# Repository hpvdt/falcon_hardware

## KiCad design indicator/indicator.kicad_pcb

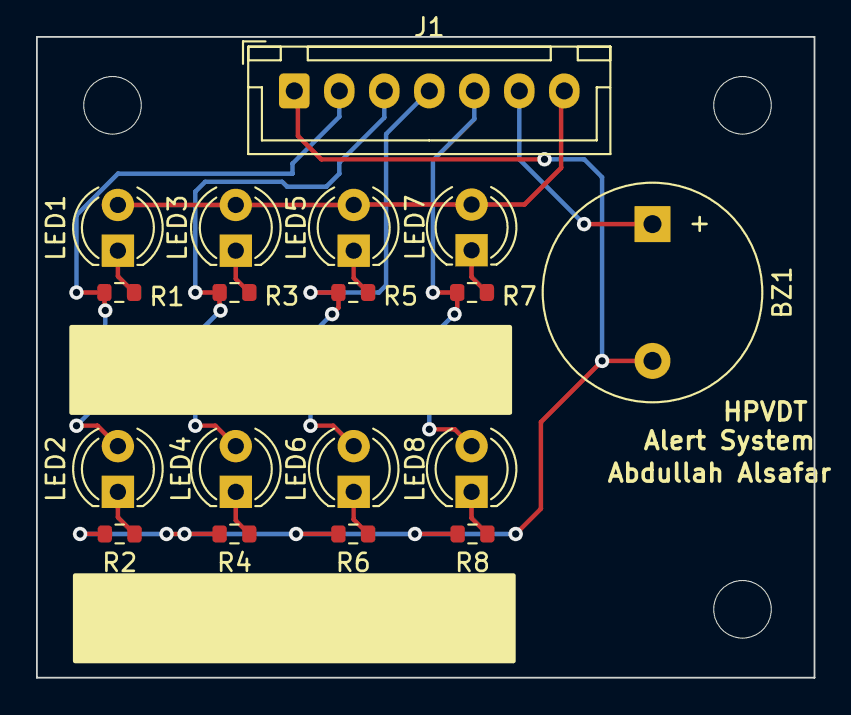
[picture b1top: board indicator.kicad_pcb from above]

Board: 2 copper layers, 43.2 x 35.6 mm, 21 parts (0 on the bottom side), 15 nets.

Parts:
BZ1: Buzzer; Buzzer_12x9.5RM7.6
HOLE1, HOLE2, HOLE3: MountingHole_3.2mm_M3
J1: Conn_01x07_Pin; JST_XH_B7B-XH-A_1x07_P2.50mm_Vertical
LED1: LED2; LED_D4.0mm
LED2: LED3; LED_D4.0mm
LED3: LED4; LED_D4.0mm
LED4: LED5; LED_D4.0mm
LED5: LED6; LED_D4.0mm
LED6: LED7; LED_D4.0mm
LED7: LED8; LED_D4.0mm
LED8: LED9; LED_D4.0mm
R1, R2, R3, R4, R5, R6, R7: 430; R_0603_1608Metric
R8: locked; R_0603_1608Metric

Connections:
+5V: J1.7, LED1.2 (A), LED3.2 (A), LED5.2 (A), LED7.2 (A)
BUZ: BZ1.1 (-), J1.6
GND: BZ1.2 (+), J1.1, R2.1, R4.1, R6.1, R8.1
LED_{FIELD1}: J1.2, LED2.2 (A), R1.1
LED_{FIELD2}: J1.3, LED4.2 (A), R3.1
LED_{FIELD3}: J1.4, LED6.2 (A), R5.1
LED_{FIELD4}: J1.5, LED8.2 (A), R7.1
unnamed: LED1.1 (K), R1.2
unnamed: LED2.1 (K), R2.2
unnamed: LED3.1 (K), R3.2
unnamed: LED4.1 (K), R4.2
unnamed: LED5.1 (K), R5.2
unnamed: LED6.1 (K), R6.2
unnamed: LED7.1 (K), R7.2
unnamed: LED8.1 (K), R8.2

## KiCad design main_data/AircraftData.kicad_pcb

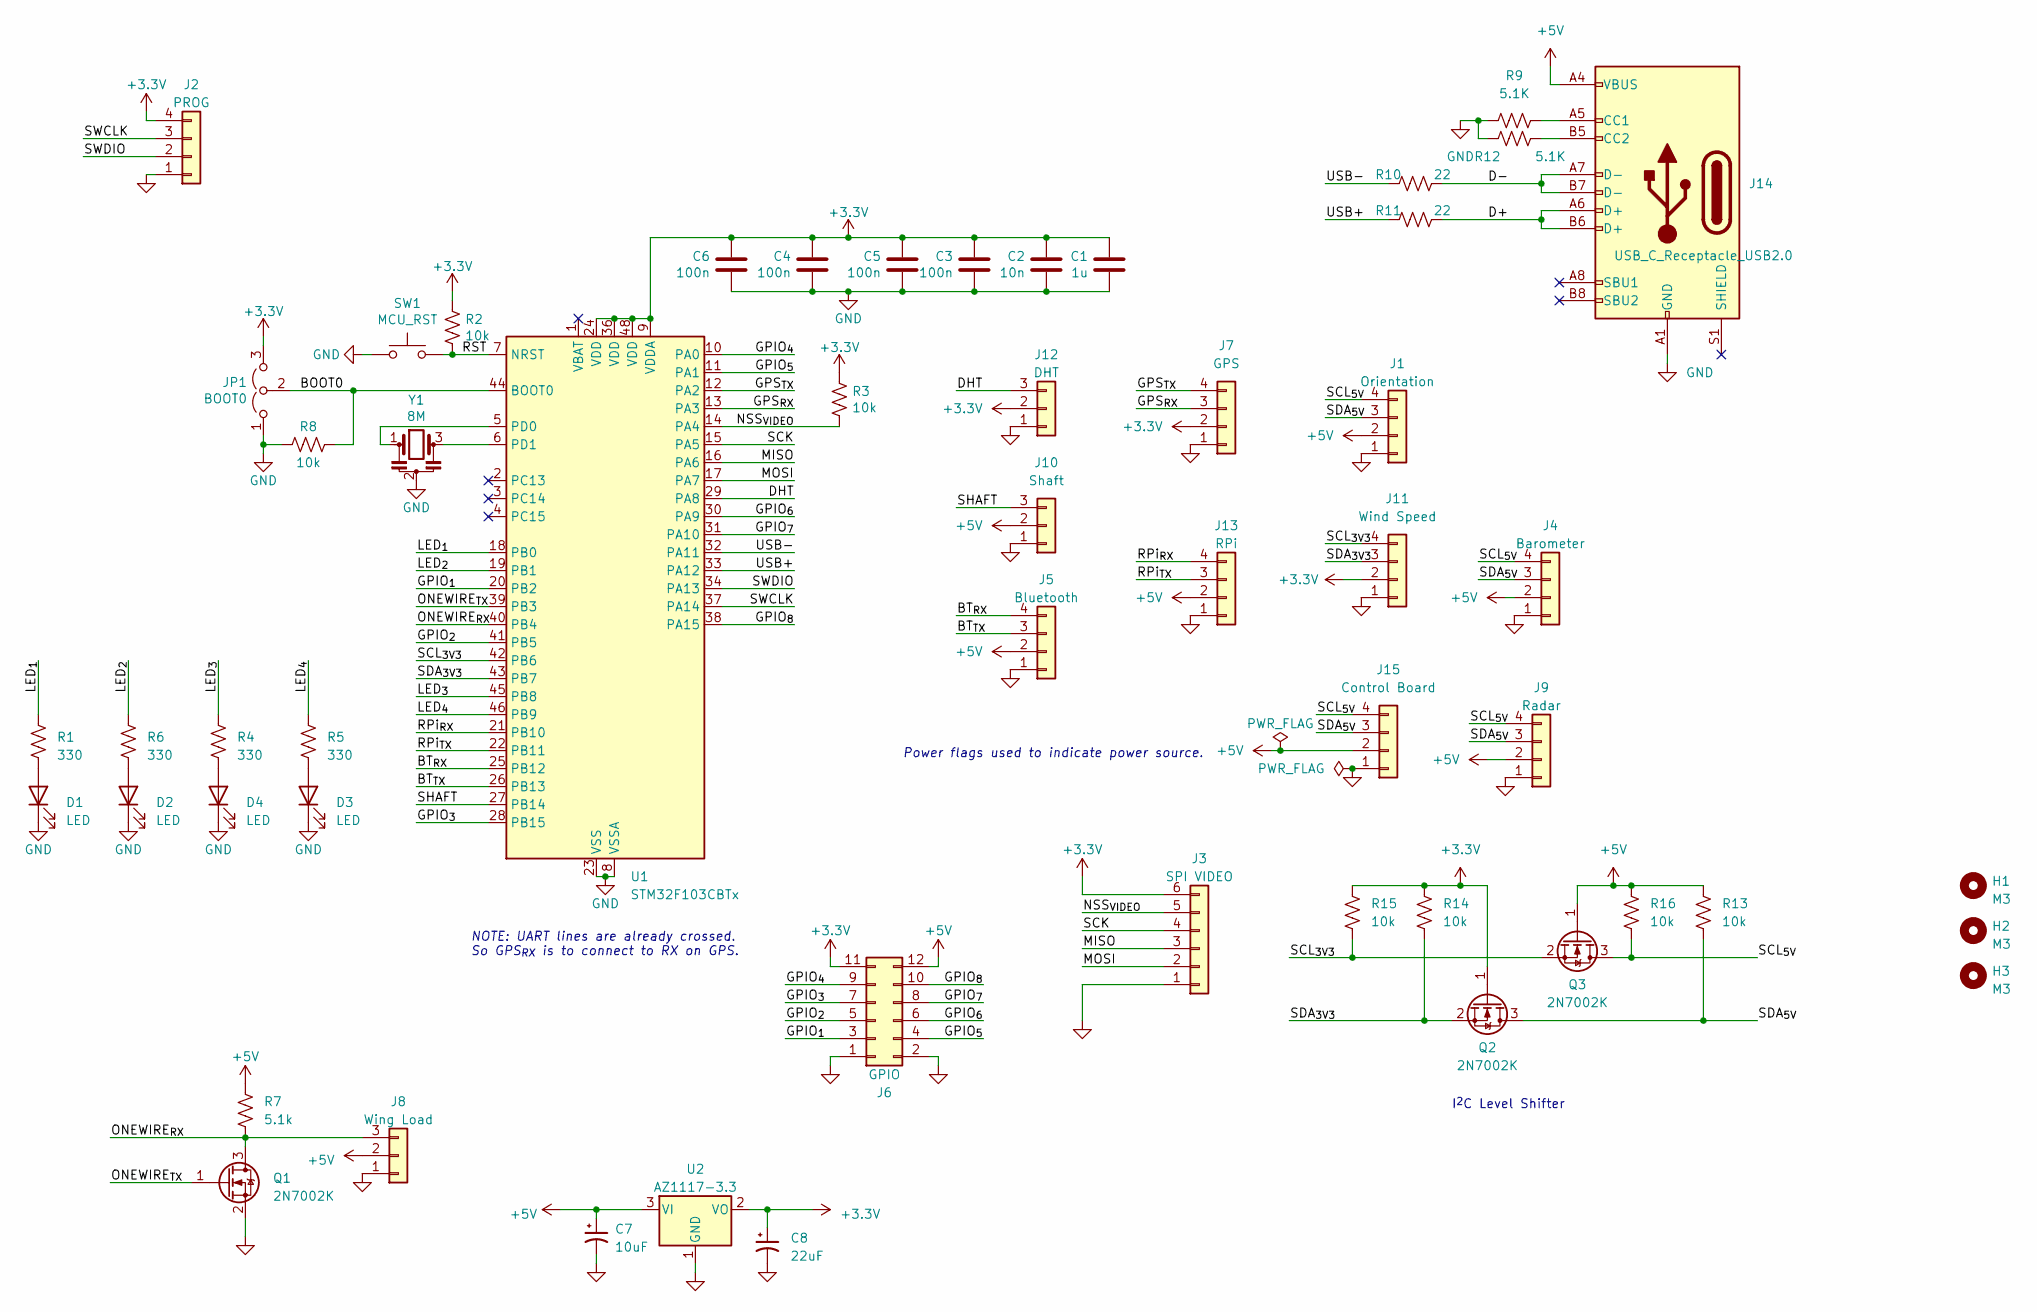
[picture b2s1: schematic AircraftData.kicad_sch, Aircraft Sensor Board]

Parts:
C1: 1u; C_0603_1608Metric
C2: 10n; C_0603_1608Metric
C3, C4, C5, C6: 100n; C_0603_1608Metric
C7: 10uF; CP_Radial_D5.0mm_P2.00mm
C8: 22uF; CP_Radial_D5.0mm_P2.00mm
D1, D2, D3, D4: LED; LED_0805_2012Metric
H1, H2, H3: M3; MountingHole_3.2mm_M3
J1: Orientation; JST_EH_B4B-EH-A_1x04_P2.50mm_Vertical
J2: PROG; JST_EH_B4B-EH-A_1x04_P2.50mm_Vertical
J3: SPI VIDEO; JST_EH_B6B-EH-A_1x06_P2.50mm_Vertical
J4: Barometer; JST_EH_B4B-EH-A_1x04_P2.50mm_Vertical
J5: Bluetooth; JST_EH_B4B-EH-A_1x04_P2.50mm_Vertical
J6: GPIO; PinHeader_2x06_P2.54mm_Vertical
J7: GPS; JST_EH_B4B-EH-A_1x04_P2.50mm_Vertical
J8: Wing Load; JST_EH_B3B-EH-A_1x03_P2.50mm_Vertical
J9: Radar; JST_EH_B4B-EH-A_1x04_P2.50mm_Vertical
J10: Shaft; JST_EH_B3B-EH-A_1x03_P2.50mm_Vertical
J11: Wind Speed; JST_EH_B4B-EH-A_1x04_P2.50mm_Vertical
J12: DHT; JST_EH_B3B-EH-A_1x03_P2.50mm_Vertical
J13: RPi; JST_EH_B4B-EH-A_1x04_P2.50mm_Vertical
J14: USB_C_Receptacle_USB2.0; USB_C_Receptacle_HRO_TYPE-C-31-M-12
J15: Control Board; JST_EH_B4B-EH-A_1x04_P2.50mm_Vertical
JP1: BOOT0; PinHeader_1x03_P2.54mm_Vertical
Q1, Q2, Q3: 2N7002K; SOT-23
R1, R4, R5, R6: 330; R_0603_1608Metric
R2, R3, R8, R13, R14, R15, R16: 10k; R_0603_1608Metric
R7: 5.1k; R_0603_1608Metric
R9, R12: 5.1K; R_0603_1608Metric
R10, R11: 22; R_0603_1608Metric
SW1: MCU_RST; SW_PUSH_6mm_H4.3mm
U1: STM32F103CBTx; LQFP-48_7x7mm_P0.5mm
U2: AZ1117-3.3; SOT-223-3_TabPin2
Y1: 8M; Resonator_SMD_Murata_CSTxExxV-3Pin_3.0x1.1mm

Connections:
+3.3V: C1.2, C2.2, C3.2, C4.2, C5.2, C6.2, C8.1, J2.4, J3.6, J6.11, J7.2, J11.2, J12.2, JP1.3 (B), Q2.1 (G), R2.2, R3.2, R14.1, R15.1, U1.9 (VDDA), U1.24 (VDD), U1.36 (VDD), U1.48 (VDD), U2.2 (VO)
+5V: C7.1, J1.2, J4.2, J5.2, J6.12, J8.2, J9.2, J10.2, J13.2, J14.A4 (VBUS), J14.A9 (VBUS), J14.B4 (VBUS), J14.B9 (VBUS), J15.2, Q3.1 (G), R7.1, R13.1, R16.1, U2.3 (VI)
/BOOT0: JP1.2 (C), R8.2, U1.44 (BOOT0)
/BT_{RX}: J5.4, U1.25 (PB12)
/BT_{TX}: J5.3, U1.26 (PB13)
/D+: J14.A6 (D+), J14.B6 (D+), R11.2
/D-: J14.A7 (D-), J14.B7 (D-), R10.2
/DHT: J12.3, U1.29 (PA8)
/GPIO_{1}: J6.3, U1.20 (PB2)
/GPIO_{2}: J6.5, U1.41 (PB5)
/GPIO_{3}: J6.7, U1.28 (PB15)
/GPIO_{4}: J6.9, U1.10 (PA0)
/GPIO_{5}: J6.4, U1.11 (PA1)
/GPIO_{6}: J6.6, U1.30 (PA9)
/GPIO_{7}: J6.8, U1.31 (PA10)
/GPIO_{8}: J6.10, U1.38 (PA15)
/GPS_{RX}: J7.3, U1.13 (PA3)
/GPS_{TX}: J7.4, U1.12 (PA2)
/LED_{1}: R1.1, U1.18 (PB0)
/LED_{2}: R6.1, U1.19 (PB1)
/LED_{3}: R4.1, U1.45 (PB8)
/LED_{4}: R5.1, U1.46 (PB9)
/MISO: J3.3, U1.16 (PA6)
/MOSI: J3.2, U1.17 (PA7)
/NSS_{VIDEO}: J3.5, R3.1, U1.14 (PA4)
/ONEWIRE_{RX}: J8.3, Q1.3 (D), R7.2, U1.40 (PB4)
/ONEWIRE_{TX}: Q1.1 (G), U1.39 (PB3)
/RPi_{RX}: J13.4, U1.21 (PB10)
/RPi_{TX}: J13.3, U1.22 (PB11)
/RST: R2.1, SW1.2, U1.7 (NRST)
/SCK: J3.4, U1.15 (PA5)
/SCL_{3V3}: J11.4, Q3.2 (S), R15.2, U1.42 (PB6)
/SCL_{5V}: J1.4, J4.4, J9.4, J15.4, Q3.3 (D), R16.2
/SDA_{3V3}: J11.3, Q2.2 (S), R14.2, U1.43 (PB7)
/SDA_{5V}: J1.3, J4.3, J9.3, J15.3, Q2.3 (D), R13.2
/SHAFT: J10.3, U1.27 (PB14)
/SWCLK: J2.3, U1.37 (PA14)
/SWDIO: J2.2, U1.34 (PA13)
/USB+: R11.1, U1.33 (PA12)
/USB-: R10.1, U1.32 (PA11)
unnamed: D1.2 (A), R1.2
unnamed: D2.2 (A), R6.2
unnamed: D3.2 (A), R5.2
unnamed: D4.2 (A), R4.2
unnamed: J14.A5 (CC1), R9.2
unnamed: J14.B5 (CC2), R12.2
unnamed: U1.5 (PD0), Y1.1
unnamed: U1.6 (PD1), Y1.3

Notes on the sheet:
NOTE: UART lines are already crossed. So GPS_{RX} is to connect to RX on GPS.
Power flags used to indicate power source.
I^{2}C Level Shifter

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
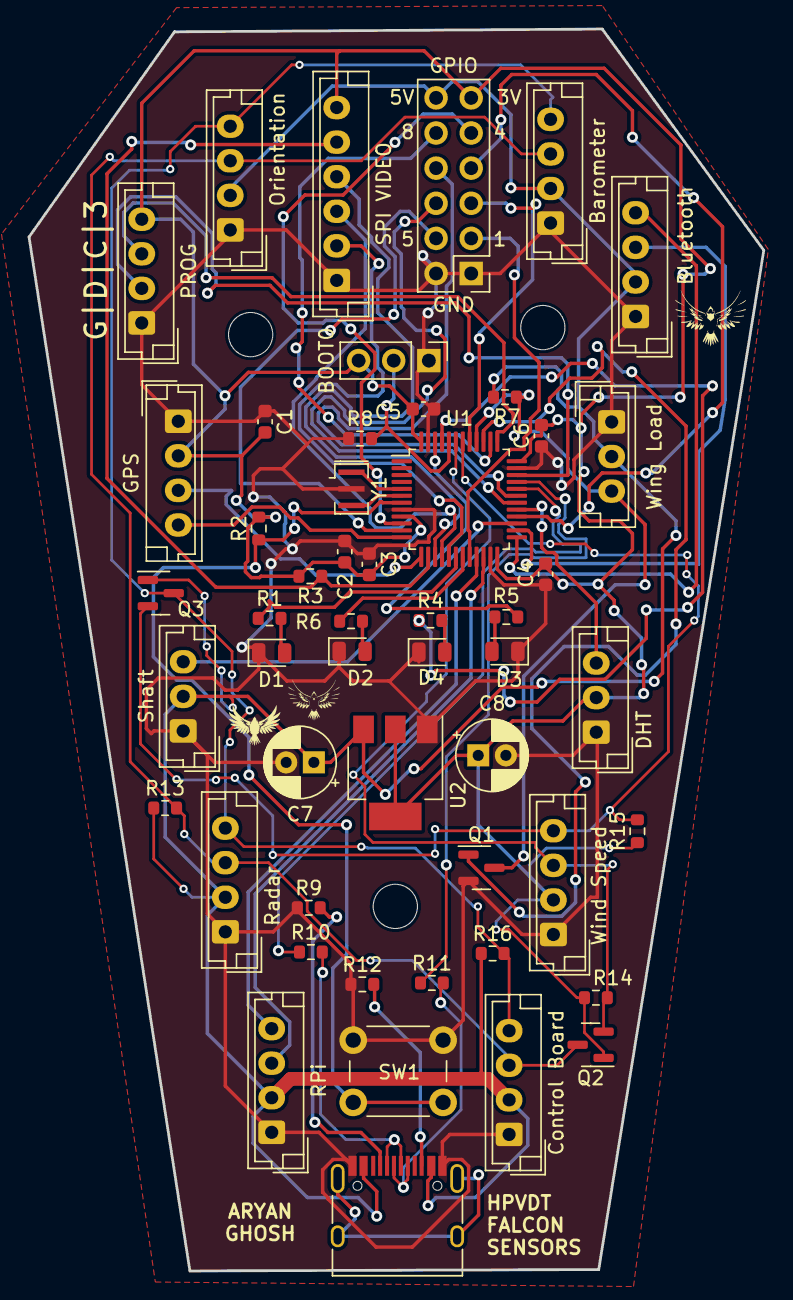
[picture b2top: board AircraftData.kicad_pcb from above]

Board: 2 copper layers, 53.1 x 89.8 mm, 54 parts (0 on the bottom side), 49 nets.

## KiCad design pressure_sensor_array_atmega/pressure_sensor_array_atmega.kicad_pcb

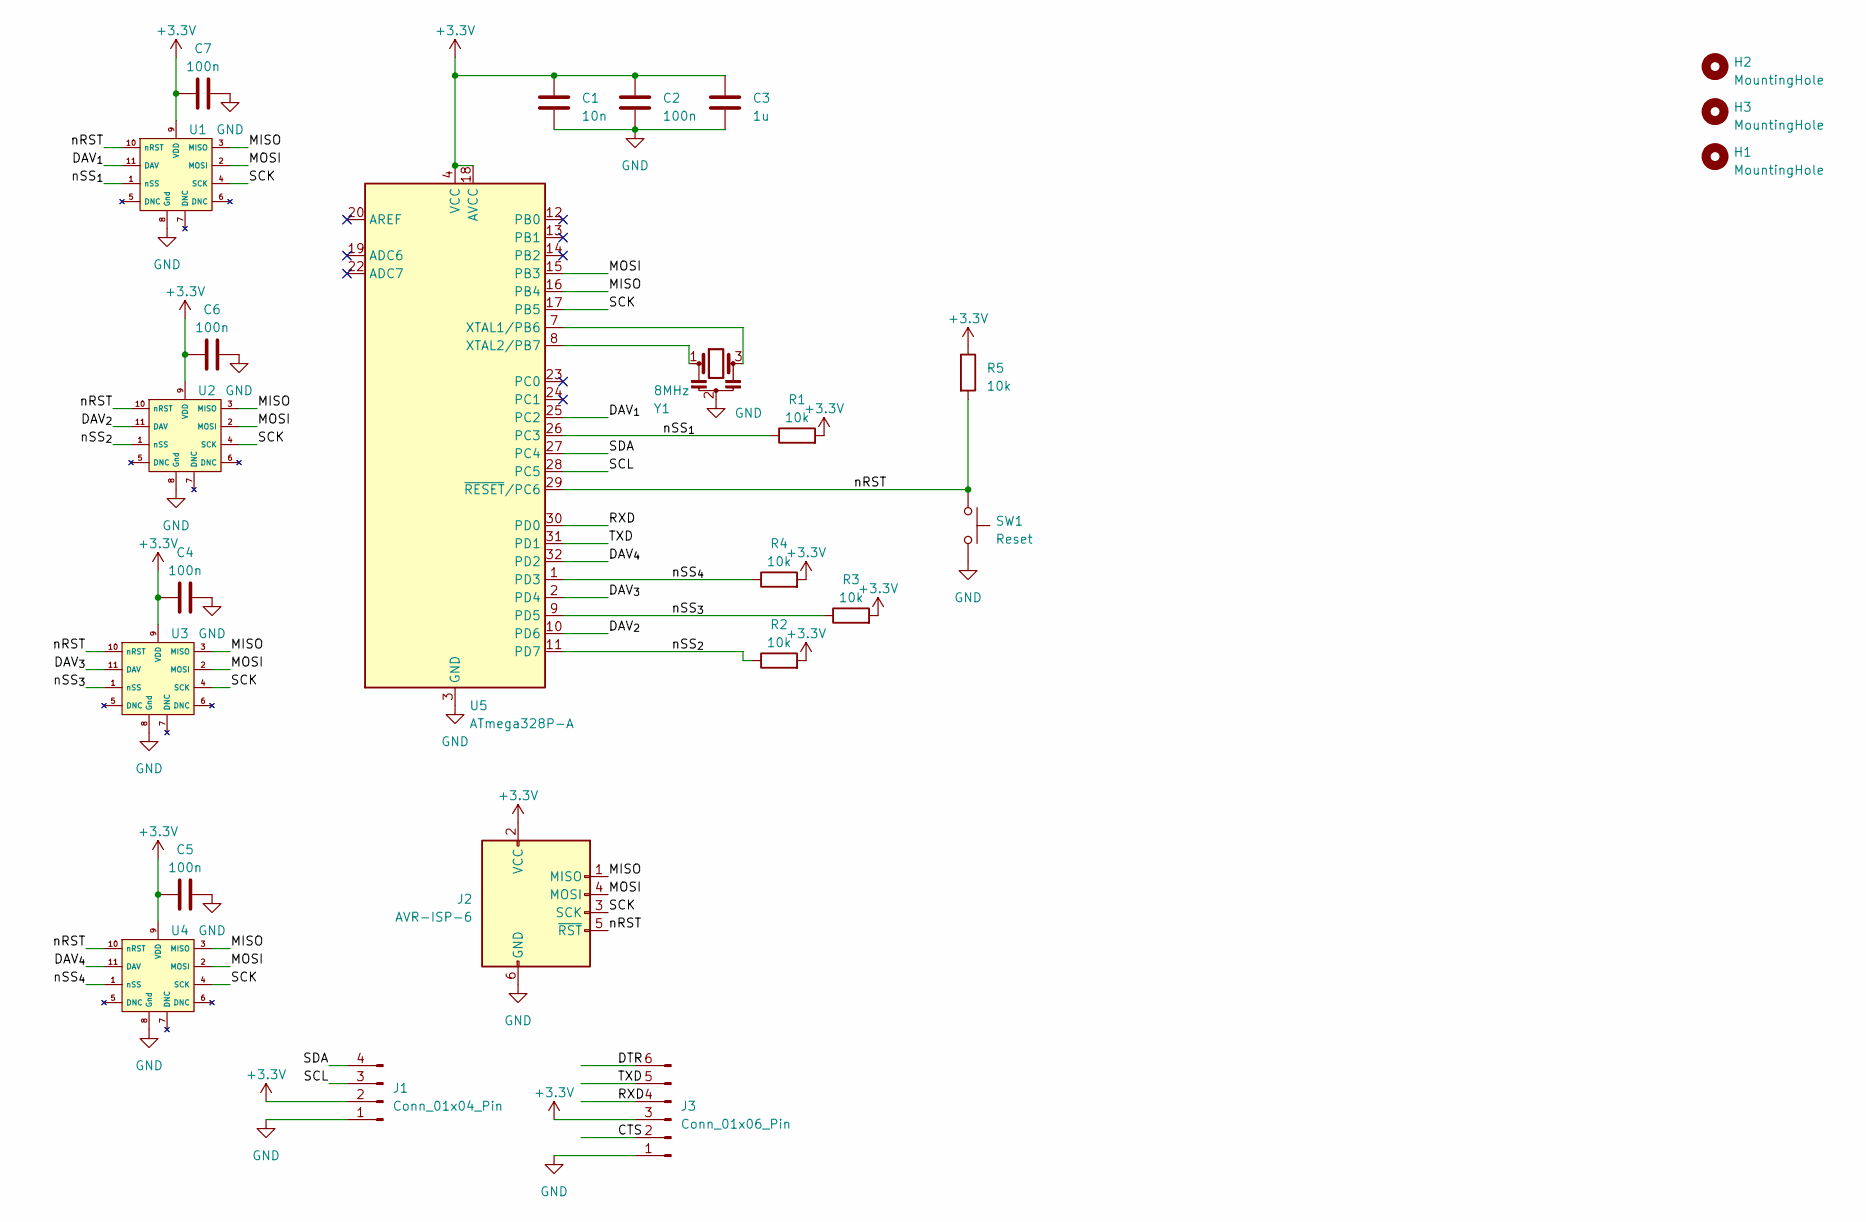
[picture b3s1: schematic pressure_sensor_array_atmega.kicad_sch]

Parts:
C1: 10n; C_0603_1608Metric
C2, C4, C5, C6, C7: 100n; C_0603_1608Metric
C3: 1u; C_0603_1608Metric
H1, H2, H3: MountingHole; MountingHole_3.2mm_M3
J1: Conn_01x04_Pin; PinHeader_1x04_P2.54mm_Vertical
J2: AVR-ISP-6; IDC-Header_2x03_P2.54mm_Vertical_SMD
J3: Conn_01x06_Pin; PinHeader_1x06_P2.54mm_Vertical
R1, R2, R3, R4, R5: 10k; R_0603_1608Metric
SW1: Reset; SW_SPST_SKQG_WithStem
U1, U2, U3, U4: HV120SM02C
U5: ATmega328P-A; TQFP-32_7x7mm_P0.8mm
Y1: 8MHz; Resonator_SMD-3Pin_7.2x3.0mm_HandSoldering

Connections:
+3.3V: C1.1, C2.1, C3.1, C4.1, C5.1, C6.1, C7.1, J1.2, J2.2 (VCC), J3.3, R1.2, R2.2, R3.2, R4.2, R5.1, U1.9 (VDD), U2.9 (VDD), U3.9 (VDD), U4.9 (VDD), U5.4 (VCC), U5.6 (VCC), U5.18 (AVCC)
/CTS: J3.2
/DAV_{1}: U1.11 (DAV), U5.25 (PC2)
/DAV_{2}: U2.11 (DAV), U5.10 (PD6)
/DAV_{3}: U3.11 (DAV), U5.2 (PD4)
/DAV_{4}: U4.11 (DAV), U5.32 (PD2)
/DTR: J3.6
/MISO: J2.1 (MISO), U1.3 (MISO), U2.3 (MISO), U3.3 (MISO), U4.3 (MISO), U5.16 (PB4)
/MOSI: J2.4 (MOSI), U1.2 (MOSI), U2.2 (MOSI), U3.2 (MOSI), U4.2 (MOSI), U5.15 (PB3)
/RXD: J3.4, U5.30 (PD0)
/SCK: J2.3 (SCK), U1.4 (SCK), U2.4 (SCK), U3.4 (SCK), U4.4 (SCK), U5.17 (PB5)
/SCL: J1.3, U5.28 (PC5)
/SDA: J1.4, U5.27 (PC4)
/TXD: J3.5, U5.31 (PD1)
/nRST: J2.5 (~RST), R5.2, SW1.1, U1.10 (nRST), U2.10 (nRST), U3.10 (nRST), U4.10 (nRST), U5.29 (~RESET/PC6)
/nSS_{1}: R1.1, U1.1 (nSS), U5.26 (PC3)
/nSS_{2}: R2.1, U2.1 (nSS), U5.11 (PD7)
/nSS_{3}: R3.1, U3.1 (nSS), U5.9 (PD5)
/nSS_{4}: R4.1, U4.1 (nSS), U5.1 (PD3)
GND: C1.2, C2.2, C3.2, C4.2, C5.2, C6.2, C7.2, J1.1, J2.6 (GND), J3.1, SW1.2, U1.8 (Gnd), U2.8 (Gnd), U3.8 (Gnd), U4.8 (Gnd), U5.3 (GND), U5.5 (GND), U5.21 (GND), Y1.2
unnamed: U5.7 (XTAL1/PB6), Y1.3
unnamed: U5.8 (XTAL2/PB7), Y1.1

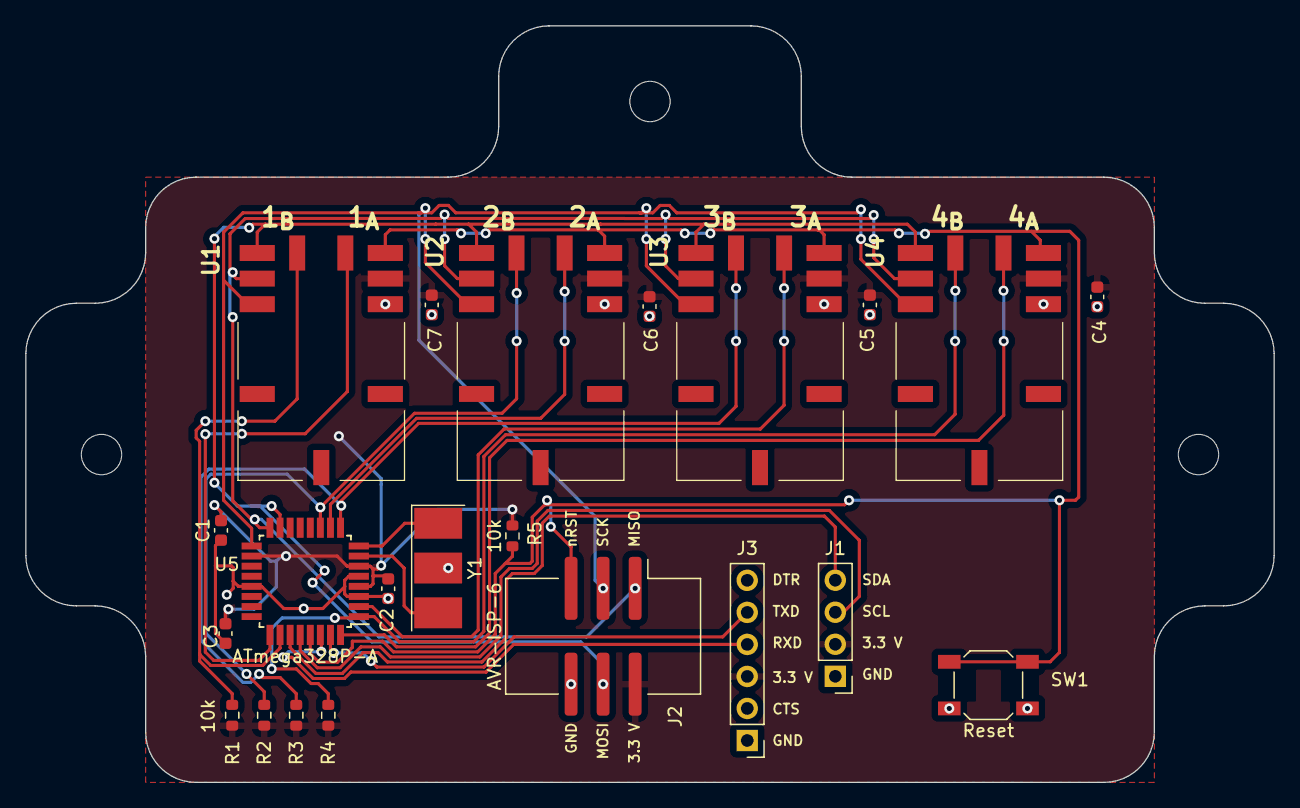
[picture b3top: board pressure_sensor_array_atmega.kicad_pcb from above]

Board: 2 copper layers, 99.0 x 60.0 mm, 25 parts (0 on the bottom side), 20 nets.

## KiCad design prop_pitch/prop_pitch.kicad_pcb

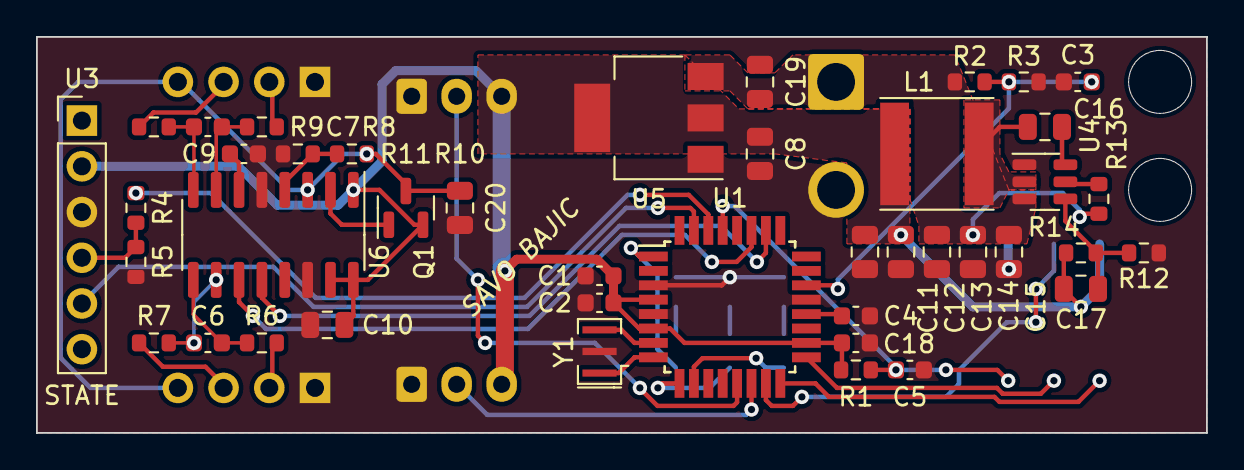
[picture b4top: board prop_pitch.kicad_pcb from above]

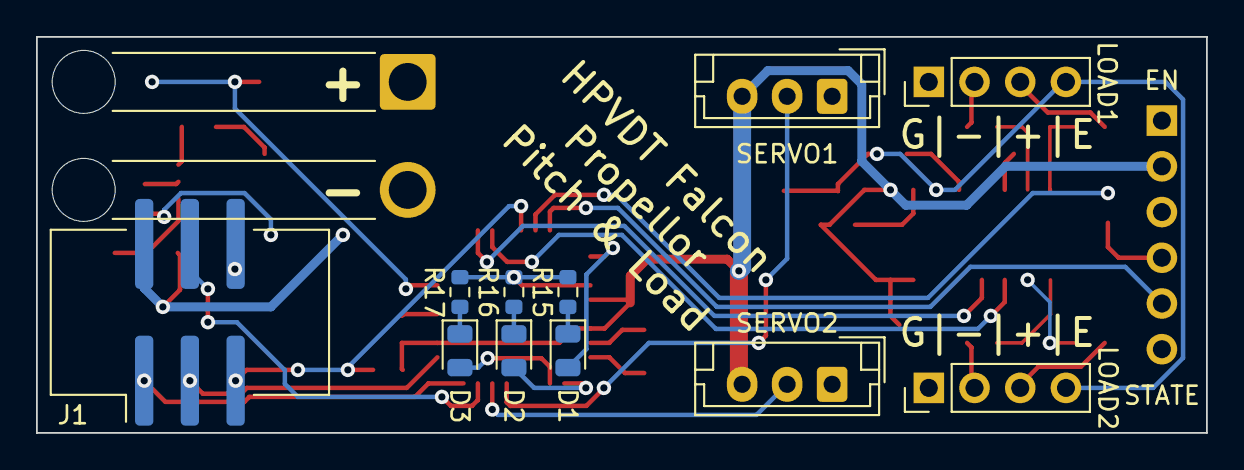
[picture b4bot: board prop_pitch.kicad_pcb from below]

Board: 2 copper layers, 65.0 x 22.0 mm, 54 parts (12 on the bottom side), 40 nets.

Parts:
BT1: Battery; SolderWire-1.5sqmm_1x02_P6mm_D1.7mm_OD3mm_Relief
C1, C5: 10n; C_0603_1608Metric
C2, C3, C4, C6, C7, C9, C18: 100n; C_0603_1608Metric
C8, C11, C12, C13, C14, C15: 22uF; C_0805_2012Metric
C10, C19, C20: 10u; C_0805_2012Metric
C16, C17: 100n; C_0805_2012Metric
D1, D2, D3: LED; LED_0805_2012Metric
J1: AVR-ISP-6; IDC-Header_2x03_P2.54mm_Vertical_SMD
J2: LOAD1; PinHeader_1x04_P2.54mm_Vertical
J3: LOAD2; PinHeader_1x04_P2.54mm_Vertical
J4: SERVO1; JST_EH_B3B-EH-A_1x03_P2.50mm_Vertical
J6: SERVO2; JST_EH_B3B-EH-A_1x03_P2.50mm_Vertical
L1: 3.3uH; L_Taiyo-Yuden_NR-60xx
Q1: MMSS8550; SOT-23
R1, R3, R5, R12, R13: 10k; R_0603_1608Metric
R2: 15k; R_0603_1608Metric
R4: 5.1k; R_0603_1608Metric
R6, R7, R8, R9: 100; R_0603_1608Metric
R10: 20k; R_0603_1608Metric
R11: 8.2k; R_0603_1608Metric
R14: 54.9k; R_0603_1608Metric
R15, R16, R17: 430; R_0603_1608Metric
U1: ATmega328P-A; TQFP-32_7x7mm_P0.8mm
U3: HC-05; PinHeader_1x06_P2.54mm_Vertical
U4: TPS563208DDCR; TSOT-23-6
U5: AZ1117-5.0; SOT-223-3_TabPin2
U6: HX711; SOP-16_3.9x9.9mm_P1.27mm
Y1: 16M; Resonator_SMD_Murata_CSTxExxV-3Pin_3.0x1.1mm

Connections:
+3.3VA: C20.2, J2.4, J3.4, Q1.3 (C), R10.1, U6.3 (AVDD)
+5V: C1.1, C2.1, C8.2, C10.2, C11.2, C12.2, C17.2, C18.1, J1.2 (VCC), J4.3, J6.3, L1.1, Q1.2 (E), R1.1, R14.1, U1.4 (VCC), U1.6 (VCC), U1.18 (AVCC), U3.2 (VCC), U5.2 (VO), U6.1 (VSUP), U6.15 (RATE), U6.16 (DVDD)
+BATT: BT1.1 (+), C13.2, C14.2, C15.2, C19.2, R2.1, R13.2, U4.3 (VIN), U5.3 (VI)
/BASE: Q1.1 (B), U6.2 (BASE)
/BATT_{SCALED}: C3.1, R2.2, R3.1, U1.22 (ADC7)
/BST: C16.2, U4.6 (VBST)
/BT_{RX}: U1.31 (PD1), U3.5 (RX)
/BT_{TX}: R4.1, U1.30 (PD0)
/DOUT_{AMP}: U1.26 (PC3), U6.12 (DOUT)
/EN: R13.1, U4.5 (EN)
/FB_{VA}: R10.2, R11.1, U6.4 (VFB)
/INA+: C7.2, R9.2, U6.8 (INA+)
/INA-: C7.1, R8.2, U6.7 (INA-)
/INB+: C6.2, R7.2, U6.10 (INB+)
/INB-: C6.1, R6.2, U6.9 (INB-)
/LED_{1}: D1.2 (A), U1.1 (PD3)
/LED_{2}: D2.2 (A), U1.9 (PD5)
/LED_{3}: D3.2 (A), U1.10 (PD6)
/MISO: J1.1 (MISO), U1.16 (PB4)
/MOSI: J1.4 (MOSI), U1.15 (PB3)
/S+_{LC1}: J2.3, R9.1
/S+_{LC2}: J3.3, R7.1
/S-_{LC1}: J2.2, R8.1
/S-_{LC2}: J3.2, R6.1
/SCK: J1.3 (SCK), U1.17 (PB5)
/SCK_{AMP}: U1.27 (PC4), U6.11 (PD_SCK)
/SERVO_{1}: J4.2, U1.13 (PB1)
/SERVO_{2}: J6.2, U1.14 (PB2)
/SW: C16.1, L1.2, U4.2 (SW)
/VFB: C17.1, R12.2, R14.2, U4.4 (VFB)
/~RESET: C5.1, J1.5 (~RST), R1.2, U1.29 (~RESET/PC6)
GND: BT1.2 (-), C1.2, C2.2, C3.2, C4.2, C5.2, C8.1, C9.1, C10.1, C11.1, C12.1, C13.1, C14.1, C15.1, C18.2, C19.1, C20.1, J1.6 (GND), J2.1, J3.1, J4.1, J6.1, R3.2, R5.2, R11.2, R12.1, R15.2, R16.2, R17.2, U1.3 (GND), U1.5 (GND), U1.21 (GND), U3.3 (GND), U4.1 (GND), U5.1 (GND), U6.5 (AGND), U6.14 (XI), Y1.2
unnamed: D1.1 (K), R15.1
unnamed: D2.1 (K), R16.1
unnamed: D3.1 (K), R17.1
unnamed: C4.1, U1.20 (AREF)
unnamed: U1.7 (XTAL1/PB6), Y1.3
unnamed: U1.8 (XTAL2/PB7), Y1.1
unnamed: R4.2, R5.1, U3.4 (TX)
unnamed: C9.2, U6.6 (VBG)

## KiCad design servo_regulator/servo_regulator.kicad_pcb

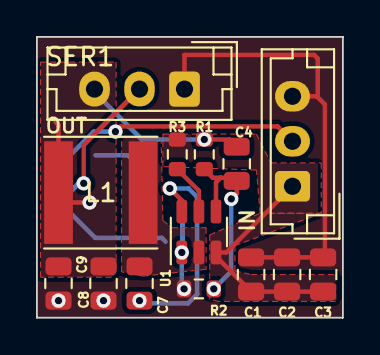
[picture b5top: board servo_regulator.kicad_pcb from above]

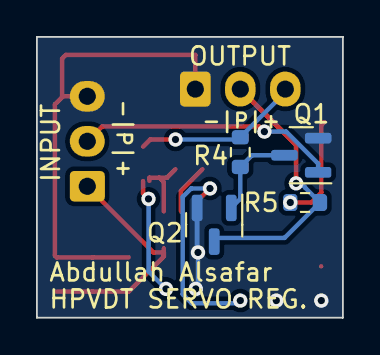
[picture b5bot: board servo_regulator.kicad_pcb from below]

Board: 2 copper layers, 17.0 x 15.6 mm, 18 parts (4 on the bottom side), 10 nets.

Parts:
C1, C2, C3, C8, C9: 22uF; C_0805_2012Metric
C4, C7: 0.1uF; C_0805_2012Metric
J1: Conn_01x03_Socket; JST_EH_B3B-EH-A_1x03_P2.50mm_Vertical
L1: 3.3uH; L_Taiyo-Yuden_NR-60xx
Q1, Q2: 2N7002K; SOT-23
R1: 54.9k; R_0603_1608Metric
R2, R3, R4: 10k; R_0603_1608Metric
R5: 5.1k; R_0603_1608Metric
SER1: Conn_01x03_Pin; JST_EH_B3B-EH-A_1x03_P2.50mm_Vertical
U1: TPS563208DDCR; TSOT-23-6

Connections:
+5V: C4.2, C8.2, C9.2, L1.1, R1.1, R4.1, R5.1, SER1.3
GND: C1.2, C2.2, C3.2, C8.1, C9.1, J1.3, Q1.2 (S), Q2.2 (S), R2.1, SER1.1, U1.1 (GND)
unnamed: C1.1, C2.1, C3.1, J1.1, R3.2, U1.3 (VIN)
unnamed: Q1.3 (D), Q2.1 (G), R4.2
unnamed: R3.1, U1.5 (EN)
unnamed: C7.1, L1.2, U1.2 (SW)
unnamed: C7.2, U1.6 (VBST)
unnamed: C4.1, R1.2, R2.2, U1.4 (VFB)
SER^{IN}: J1.2, Q1.1 (G)
SER^{OUT}: Q2.3 (D), R5.2, SER1.2
